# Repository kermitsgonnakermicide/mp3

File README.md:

# PiMP3

A Pi based MP3 player, with a touchscreen display and a couple of mechanical keys(+ encoder!)<br>

I wanted to make a desktop mp3 player, something that I could use on my table or in the living room as a stand alone music player.

**Design**<br>
I wanted to use a Pi Zero 2 W because I saw [this](https://www.waveshare.com/3.5inch-rpi-lcd-g.htm) awesome display and wanted to structure my player around this.<br>
I made a wee little PCB for mounting my mechanical keys and encoder<br>
<br>
And for attaching both of these, I made a case<br>

**Software**
The python script(s) loads MP3 files, extracts their metadata and album art, and displays them on a 3.5" LCD. Our mechanical keys let you scroll and select songs, while a rotary encoder adjusts the volume. On selection, the music_display module handles playback using the chosen song.

**BOM**<Br>
| [S.NO](http://s.no/) | ITEM | QTY | UNIT PRICE | TOTAL | SRC |
| -------------------- | ---------------------- | --- | ---------- | ----- | ------------------------------------------------------------------------------------------------------------------------------------------------------------------------------------------------------------------------------------------------------------------------------------------------------------------------------------------------------------------------------------------------------------------------------------------------------------------------------------------------------------------------------------------------------------------------------------------------------------------------------------------------------------------------------------------------------------------------------------------------------------------------------------------------------------------------------------------------------------------------------------------------------------------------------------------------------------------------------------------------------------------------------------------------------------ |
| 1 | Raspberry Pi Zero 2 W | 1 | 20.52 | 20.52 | [https://www.silverlineelectronics.in/collections/the-raspberry-pi/products/raspberry-pi-zero-2w-basic-pack-raspberry-pi-zero-2w-max-1-per-customer-per-month-in-stock](https://www.silverlineelectronics.in/products/raspberry-pi-4-model-b-4gb-silverline-india?variant=40981686452393) |
| 2 | 3.5 inch LCD module | 1 | 18.54 | 18.54 | [https://hubtronics.in/3.5inch-rpi-lcd-g](https://hubtronics.in/3.5inch-rpi-lcd-g) |
| 3 | HMX Macchiato Switches | 1 | 3.48 | 3.48 | [https://neomacro.in/products/hmx-macchiato-linear-switch](https://neomacro.in/products/hmx-macchiato-linear-switch) |
| 4 | EC11 Encoder | 1 | 2.06 | 2.06 | [https://www.amazon.in/CentIoT-Encoder-Digital-Potentiometer-Control/dp/B0888RVZSN/ref=sr_1_1?dib=eyJ2IjoiMSJ9.ub-gVfIJkebgtPjQTQbP-1BNXrl39Ma9zP8YixnEs_tw0VYc10gQvY7xqzuh_vZceHd2y-6J9D-NB9MjzyDwMGJIKOrWb9IZEiOruOY8D37diZ-Mi-mWW6Ih14xuLm8STNjV2h-nbaJC9DMzZgZoX5PxpEv7ul9Q4GGyM7gzU9TtIZhDOw5A-AdJKh8g-Y8ljjHBeLH-eLWOzSZ4Ftt-ZvcS2EI1YVhMKyesSluyfP6xULgmHWb_qcBHdLBGNNxqSWQYmD_pLOQnpAjRdksGop-jiegdd_lhKNFeYlihQNs.C6u3HSLR85ezz9IoDRMTJXpV3etCnDG9RNMFscjRzxA&dib_tag=se&keywords=EC11+encoder&qid=1749897251&sr=8-1](https://www.amazon.in/CentIoT-Encoder-Digital-Potentiometer-Control/dp/B0888RVZSN/ref=sr_1_1?dib=eyJ2IjoiMSJ9.ub-gVfIJkebgtPjQTQbP-1BNXrl39Ma9zP8YixnEs_tw0VYc10gQvY7xqzuh_vZceHd2y-6J9D-NB9MjzyDwMGJIKOrWb9IZEiOruOY8D37diZ-Mi-mWW6Ih14xuLm8STNjV2h-nbaJC9DMzZgZoX5PxpEv7ul9Q4GGyM7gzU9TtIZhDOw5A-AdJKh8g-Y8ljjHBeLH-eLWOzSZ4Ftt-ZvcS2EI1YVhMKyesSluyfP6xULgmHWb_qcBHdLBGNNxqSWQYmD_pLOQnpAjRdksGop-jiegdd_lhKNFeYlihQNs.C6u3HSLR85ezz9IoDRMTJXpV3etCnDG9RNMFscjRzxA&dib_tag=se&keywords=EC11+encoder&qid=1749897251&sr=8-1) |
| 5 | M2.5 Bolt | 10 | 0.6 | 6 | [https://3fparts.com/shop/m2-5-50mm-socket-head-allen-bolt-cap-screw-din-912-stainless-steel-304-a2-70](https://3fparts.com/shop/m2-5-50mm-socket-head-allen-bolt-cap-screw-din-912-stainless-steel-304-a2-70) |
| 6 | PCB | 1 | ~20 | 20 | what it cost for my last PCB |
| | | | | 70.6 | |

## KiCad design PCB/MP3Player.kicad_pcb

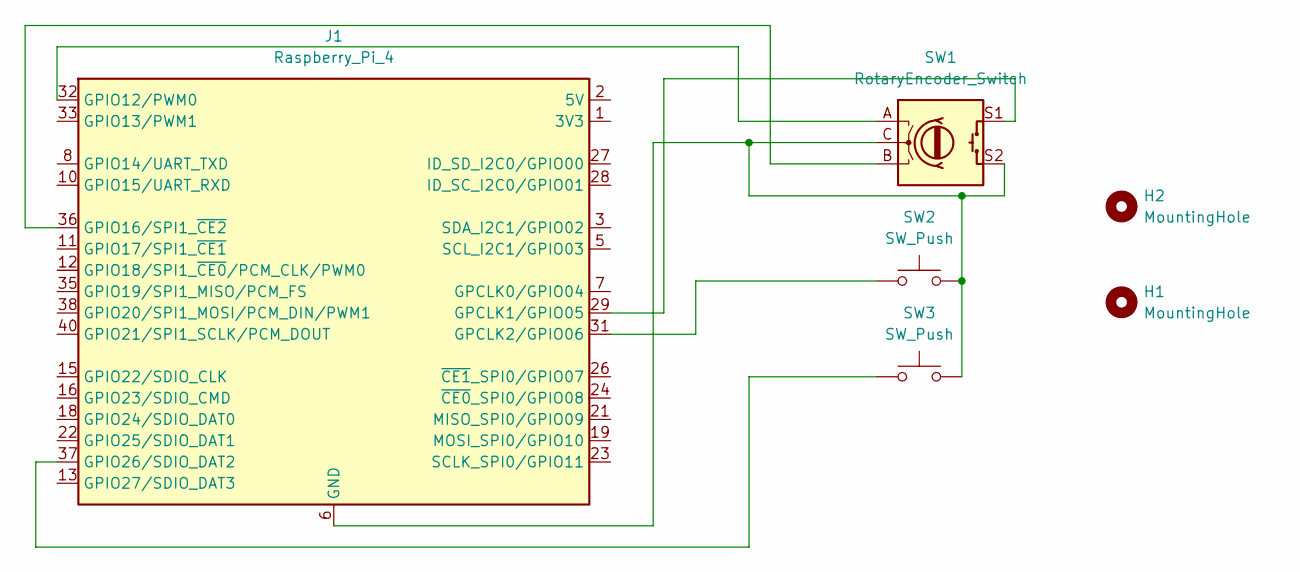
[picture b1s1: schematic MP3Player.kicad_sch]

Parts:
H1, H2: MountingHole; MountingHole_2.2mm_M2
J1: Raspberry_Pi_4; PinSocket_2x20_P2.54mm_Vertical
SW1: RotaryEncoder_Switch; RotaryEncoder_Alps_EC11E-Switch_Vertical_H20mm_MountingHoles
SW2, SW3: SW_Push; SW_Cherry_MX_1.00u_PCB

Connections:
unnamed: J1.1 (3V3), J1.17 (3V3)
unnamed: J1.2 (5V), J1.4 (5V)
unnamed: J1.6 (GND), J1.9 (GND), J1.14 (GND), J1.20 (GND), J1.25 (GND), J1.30 (GND), J1.34 (GND), J1.39 (GND), SW1.C, SW1.S2, SW2.2, SW3.2
unnamed: J1.29 (GPCLK1/GPIO05), SW1.S1
unnamed: J1.31 (GPCLK2/GPIO06), SW2.1
unnamed: J1.32 (GPIO12/PWM0), SW1.A
unnamed: J1.36 (GPIO16/SPI1_~CE2), SW1.B
unnamed: J1.37 (GPIO26/SDIO_DAT2), SW3.1

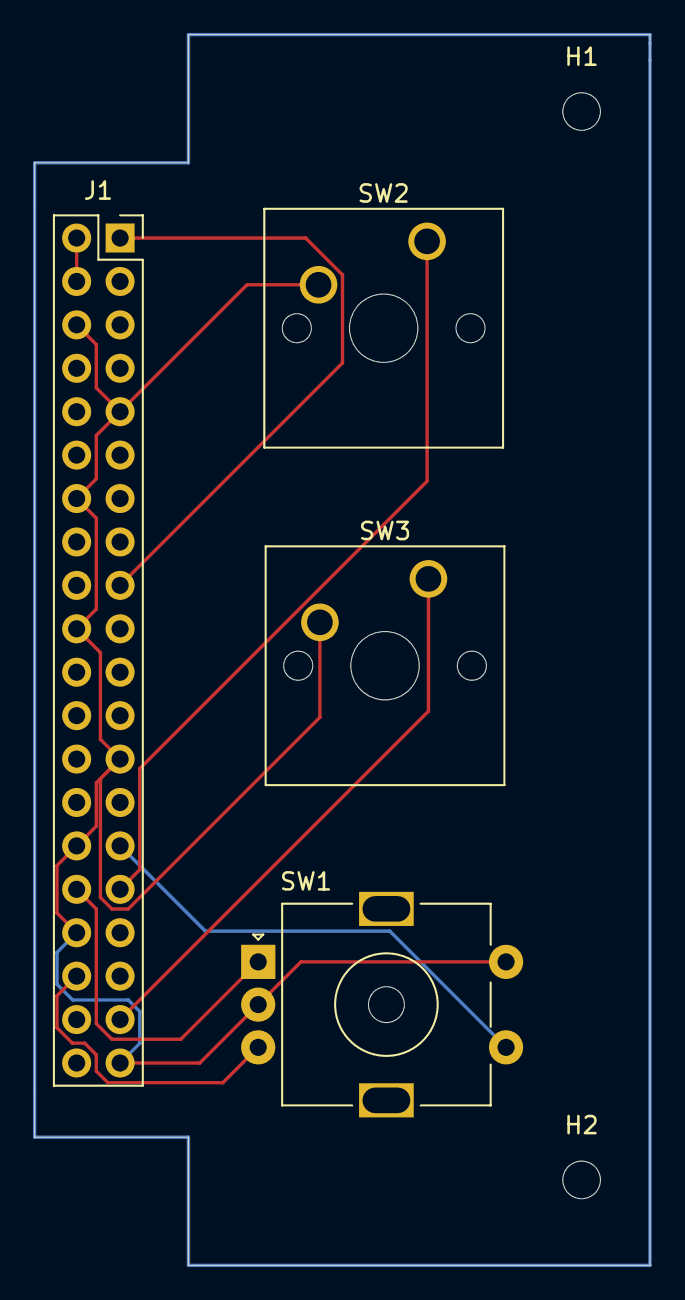
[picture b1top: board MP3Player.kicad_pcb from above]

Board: 2 copper layers, 36.0 x 72.0 mm, 6 parts (0 on the bottom side), 8 nets.

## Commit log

2025-06-09 baguette(pcb stuff and reorganisation)
2025-06-09 drill holes
2025-06-10 aaaaaa
2025-06-10 git hurts me
2025-06-13 epik!!
2025-06-14 update!
2025-06-14 final
2025-06-17 update!!
